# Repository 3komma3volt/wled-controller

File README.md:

# wled-controller
A small ESP8266 controller with step-down for use with [WLED](https://github.com/Aircoookie/WLED) firmware made with KICAD 6

# Intro
This board was designed for a christmas lightshow and 17 of them were used. They were supplied from a central 24V power supply and the supply was chained from prop to prop. This made wireing very easy. 
The included 5V regulator supplies up to 5A which is pretty enough for some light props.
The [KICAD](https://www.kicad.org) files include LCSC component numbers for direct ordering at [JLCPCB](https://jlcpcb.com)
The board shape is made for some cheap enclosures

# Usage
First decide if you want to use the voltage regulator. In some cases, you need more power and then you can remove/not populate the U4 regulator and solder the 5V_Bridge1 on the board. Then the VIN supply must not more than 12V!
With the brige, the voltage on the screw terminals is the same than VIN. So you could use 12V pixels whith this board or a powerful 5V supply. The ESP is supplied from an other voltage regulator.
Without brige, the voltage regulator has to be mounted. Use following fusing for F1:
- 24V input: 1.3A
- 5V or 12V input (with bridge and no U4 mounted): 5A or greater, accordingly to your used power supply / or pixels
An OLED can be mounted but have to be defined in the firmware
A MOSFET can be populated and switch some small loads (connected to J3) and have to be defined in firmware

## Programming
For programming an USB to UART converter is needed. Use following steps:
- EITHER supply from VIN or supply 3.3V to J2 (e.g. from an USB/UART converter)
- Connect GND, RX, TX from the USB/UART to J2
- Press and hold PG, press and release RS, release RS. The EPS should now be in programming mode
- Program accordingly WLED manual and press RS after programming. Now the board should open an AP

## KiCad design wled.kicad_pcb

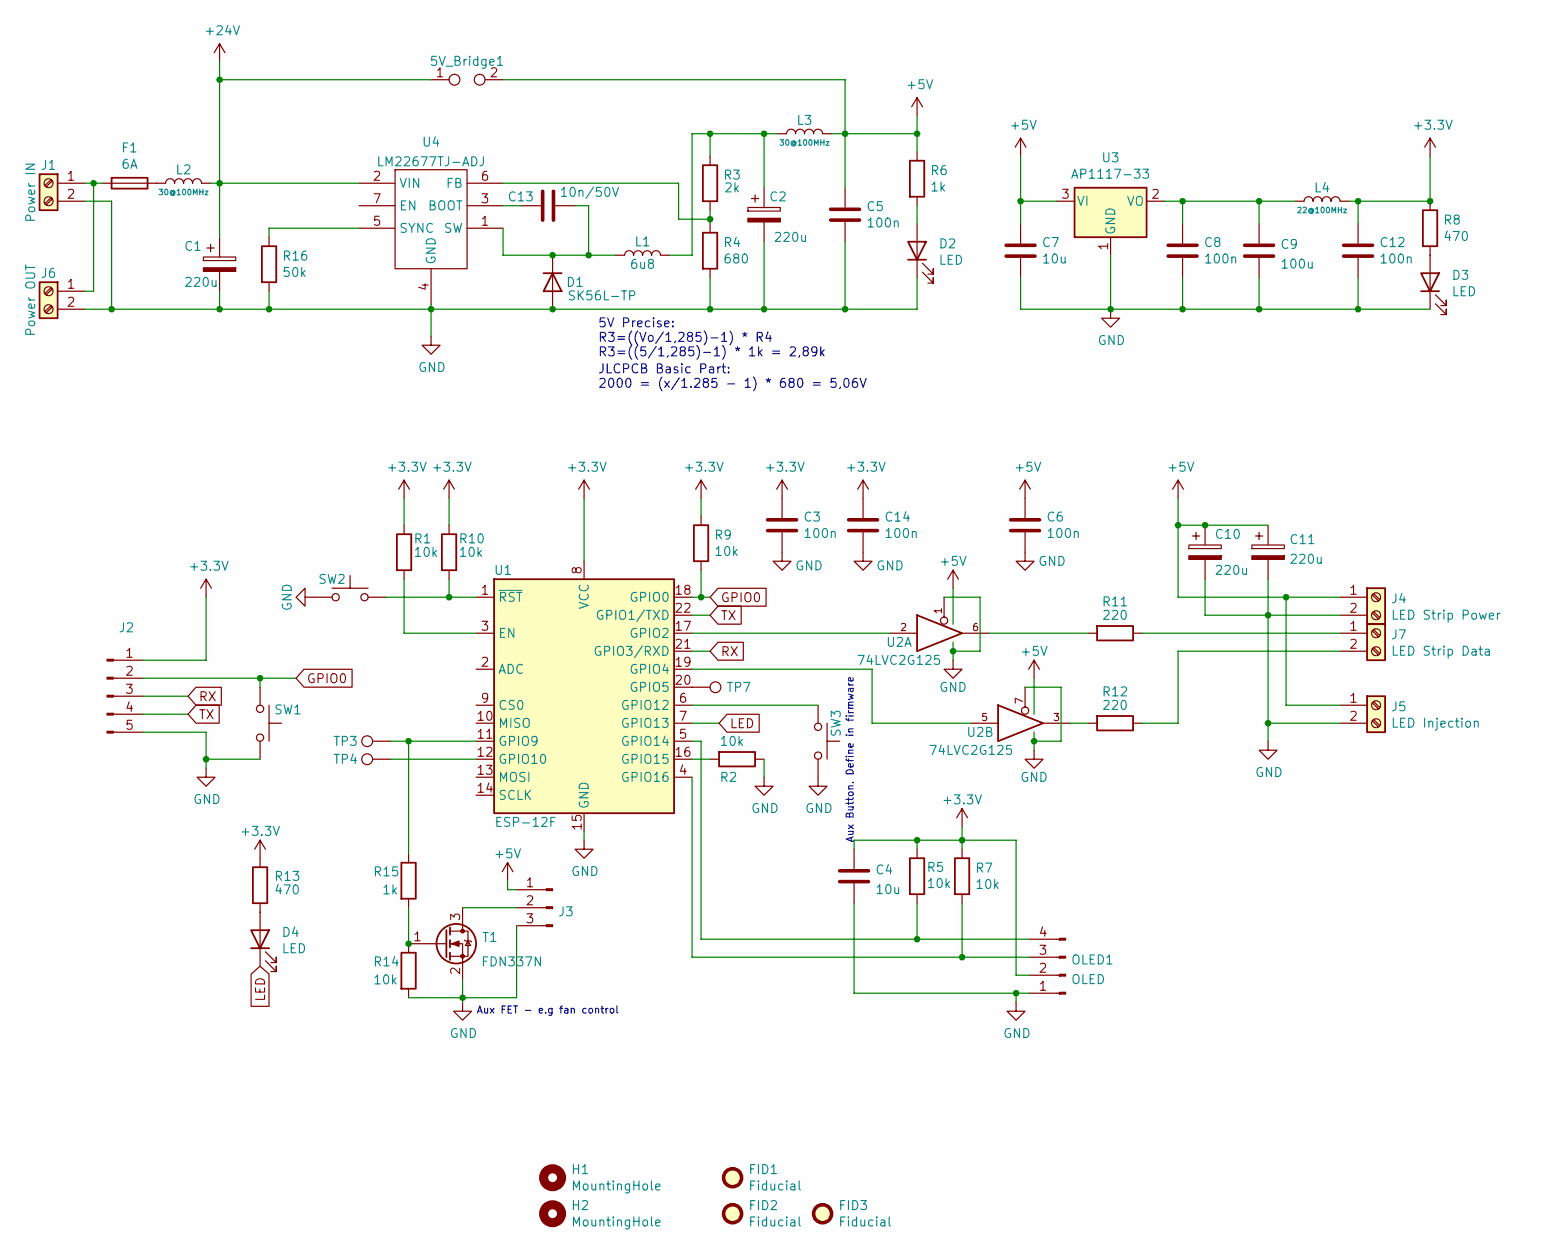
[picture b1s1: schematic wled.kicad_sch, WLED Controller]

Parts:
5V_Bridge1: TestPoint_2Pole; TestPoint_2Pads_Pitch5.08mm_Drill1.3mm
C1, C2, C10, C11: 220u; CP_Elec_8x10; LCSC C311611
C3, C5, C6, C8, C12, C14: 100n; C_0603_1608Metric; LCSC C14663
C4: 10u; C_1206_3216Metric; LCSC C19702
C7: 10u; C_0805_2012Metric; LCSC C19702
C9: 100u; C_1210_3225Metric; LCSC C16133
C13: 10n/50V; C_0603_1608Metric; LCSC C57112
D1: SK56L-TP; D_SMC; LCSC C669020
D2, D3, D4: LED; LED_0603_1608Metric; LCSC C72038
F1: 6A; FX0321
FID1, FID2, FID3: Fiducial; Fiducial_0.75mm_Mask1.5mm
H1, H2: MountingHole; MountingHole_4.3mm_M4
J1: Power IN; OSTTC020162
J2: Conn_01x05_Male; PinHeader_1x05_P2.54mm_Vertical
J3: Conn_01x03_Male; JST_PH_B3B-PH-K_1x03_P2.00mm_Vertical
J4: LED Strip Power; OSTTC020162
J5: LED Injection; OSTTC020162
J6: Power OUT; OSTTC020162
J7: LED Strip Data; OSTTC020162
L1: 6u8; L_10.4x10.4_H4.8; LCSC C207852
L2, L3: 30@100MHz; L_1206_3216Metric; LCSC C316417
L4: 22@100MHz; L_0603_1608Metric; LCSC C73100
OLED1: OLED; 128x64OLED
R1, R2, R5, R7, R9, R10, R14: 10k; R_0603_1608Metric; LCSC C25804
R3: 2k; R_0603_1608Metric; LCSC C22975
R4: 680; R_0603_1608Metric; LCSC C23228
R6, R15: 1k; R_0603_1608Metric; LCSC C21190
R8, R13: 470; R_0603_1608Metric; LCSC C23179
R11, R12: 220; R_0603_1608Metric; LCSC C22962
R16: 50k; R_0603_1608Metric; LCSC C23196
SW1, SW2, SW3: SW_Push; SW_SPST_CK_RS282G05A3; LCSC C520860
T1: FDN337N; SOT-23; LCSC C475694
TP3, TP4, TP7: TestPoint; TestPoint_THTPad_D1.5mm_Drill0.7mm
U1: ESP-12F; ESP-12E; LCSC C82891
U2: 74LVC2G125; TSSOP-8_3x3mm_P0.65mm; LCSC C206035
U3: AP1117-33; SOT-223-3_TabPin2; LCSC C6186
U4: LM22677TJ-ADJ; TO-263-7_TabPin4

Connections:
+3V3: C3.1, C4.1, C12.1, C14.1, J2.1, L4.2, OLED1.2, R1.1, R5.1, R7.1, R8.1, R9.1, R10.1, R13.1, U1.8 (VCC)
+5V: 5V_Bridge1.2, C5.1, C6.1, C7.1, C10.1, C11.1, J3.1, J4.1, J5.1, L3.2, R6.1, U2.8 (VCC), U3.3 (VI)
+24V: 5V_Bridge1.1, C1.1, L2.2, U4.2 (VIN)
GND: C1.2, C2.2, C3.2, C4.2, C5.2, C6.2, C7.2, C8.2, C9.2, C10.2, C11.2, C12.2, C14.2, D1.2 (A), D2.1 (K), D3.1 (K), J1.2, J2.5, J3.3, J4.2, J5.2, J6.2, OLED1.1, R2.1, R4.2, R14.2, R16.2, SW1.2, SW2.2, SW3.1, T1.2 (S), U1.15 (GND), U2.1, U2.4 (GND), U2.7, U3.1 (GND), U4.4 (GND)
GPIO0: J2.2, R9.2, SW1.1, U1.18 (GPIO0)
LED: D4.1 (K), U1.7 (GPIO13)
unnamed: C2.1, L1.2, L3.1, R3.1
unnamed: C8.1, C9.1, L4.1, U3.2 (VO)
unnamed: C13.1, U4.3 (BOOT)
unnamed: C13.2, D1.1 (K), L1.1, U4.1 (SW)
unnamed: D2.2 (A), R6.2
unnamed: D3.2 (A), R8.2
unnamed: D4.2 (A), R13.2
unnamed: F1.1, L2.1
unnamed: F1.2, J1.1, J6.1
unnamed: J3.2, T1.3 (D)
unnamed: J7.1, R11.1
unnamed: J7.2, R12.1
unnamed: OLED1.3, R7.2, U1.4 (GPIO16)
unnamed: OLED1.4, R5.2, U1.5 (GPIO14)
unnamed: R1.2, U1.3 (EN)
unnamed: R2.2, U1.16 (GPIO15)
unnamed: R3.2, R4.1, U4.6 (FB)
unnamed: R10.2, SW2.1, U1.1 (~RST)
unnamed: R11.2, U2.6
unnamed: R12.2, U2.3
unnamed: R14.1, R15.2, T1.1 (G)
unnamed: R15.1, TP3.1, U1.11 (GPIO9)
unnamed: R16.1, U4.5 (SYNC)
unnamed: SW3.2, U1.6 (GPIO12)
unnamed: TP4.1, U1.12 (GPIO10)
unnamed: TP7.1, U1.20 (GPIO5)
unnamed: U1.17 (GPIO2), U2.2
unnamed: U1.19 (GPIO4), U2.5
RX: J2.3, U1.21 (GPIO3/RXD)
TX: J2.4, U1.22 (GPIO1/TXD)

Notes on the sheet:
Aux Button. Define in firmware
JLCPCB Basic Part: 2000 = (x/1.285 - 1) * 680 = 5,06V
5V Precise: R3=((Vo/1,285)-1) * R4 R3=((5/1,285)-1) * 1k = 2,89k
Aux FET - e.g fan control

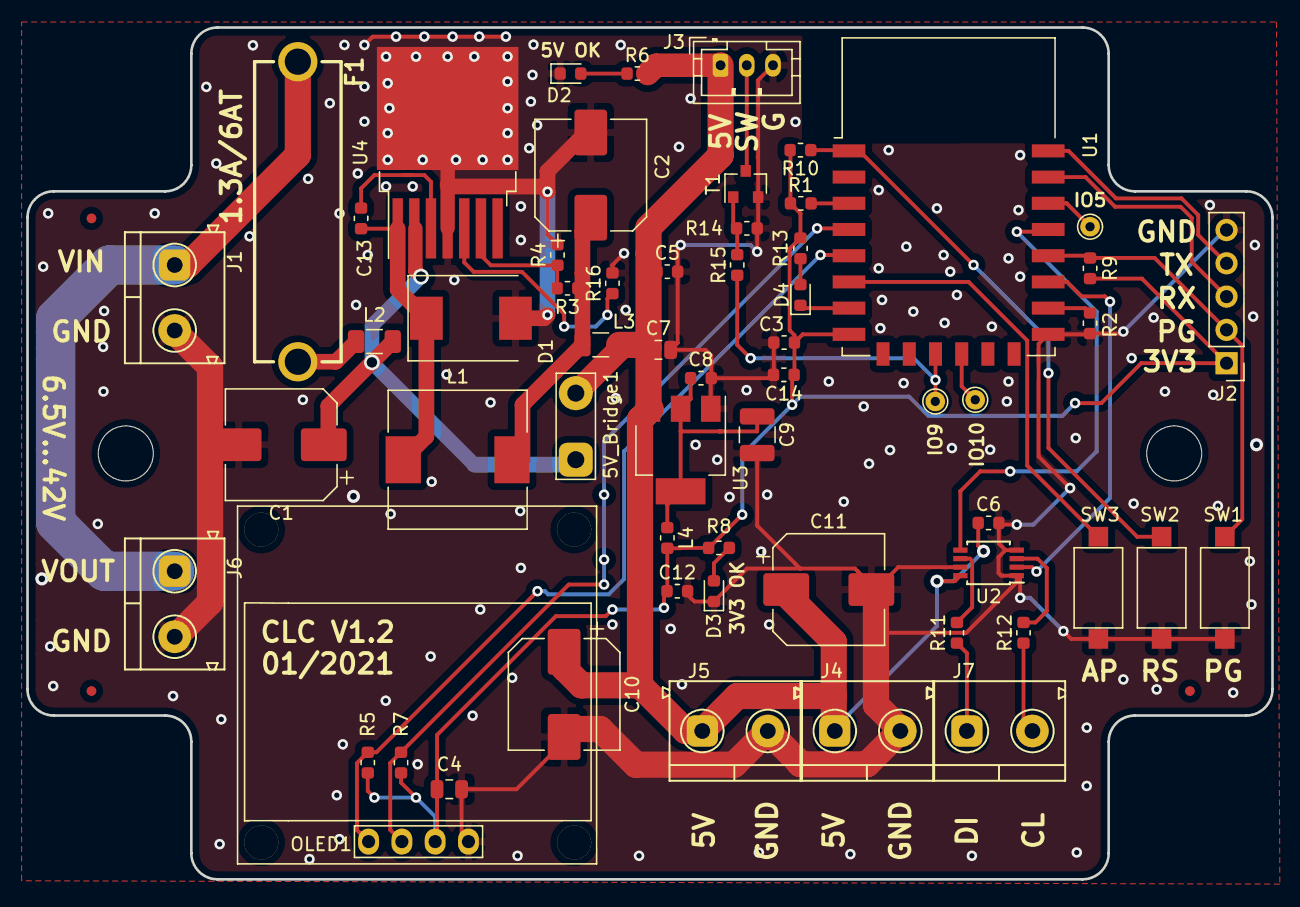
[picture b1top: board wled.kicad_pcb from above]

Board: 2 copper layers, 95.0 x 65.0 mm, 64 parts (0 on the bottom side), 36 nets.
